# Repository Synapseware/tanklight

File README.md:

tanklights
==========

Tanklights is a fun project for adding moonlight lighting effects to a fish tank, or other environment where having an undulating lighting effect is desirable.  When properly laid out, the lighting is meant to be a rough simulation of what moonlight might look like under water.

The hardware/LEDs are wired up in a charlieplexed format.  Using just 3 pins of the micro controller (an Atmel ATTiny13), 6 LEDs can be individually controller.

The formula for the total number of LEDs is given by n^2-n, where n is the number of pins.  So, 3^2-3 = 6.

Read more about charlieplexing here: https://en.wikipedia.org/wiki/Charlieplexing

The lighting effects are accomplished by very fast switching of the LED matrix, so that persistence of vision plays a key role in the apparent light levels of the LEDs.

## building
The project has a simple Makefile.  It is currently configured to compiled under Linux only (but could be easily modified for other operating systems).  You will need to install AVRA, which is the open source equivalent of the Atmel AVR Assembler, avrasm.exe, that is included with AVR Studio for Windows.

### AVRA
Avra can also be installed easily on Linux:  `apt install -y avra` for Debian based systems.  The AVRA project home is here: http://avra.sourceforge.net/

### Atmel AVR Assembler
http://www.atmel.com/webdoc/avrassembler/index.html

### Other notes
The main idea with this project is not to build yet another LED blinking hello-world type of application, but is more a demonstration of what you can build using assembly and very lower powered micro-controllers.  Current code size is 640 bytes, or 320 words.  The timers on the ATTiny13 are used to advance or cycle through the lighting pattern, while the main charlieplexing display driver code is left to run at full speed.

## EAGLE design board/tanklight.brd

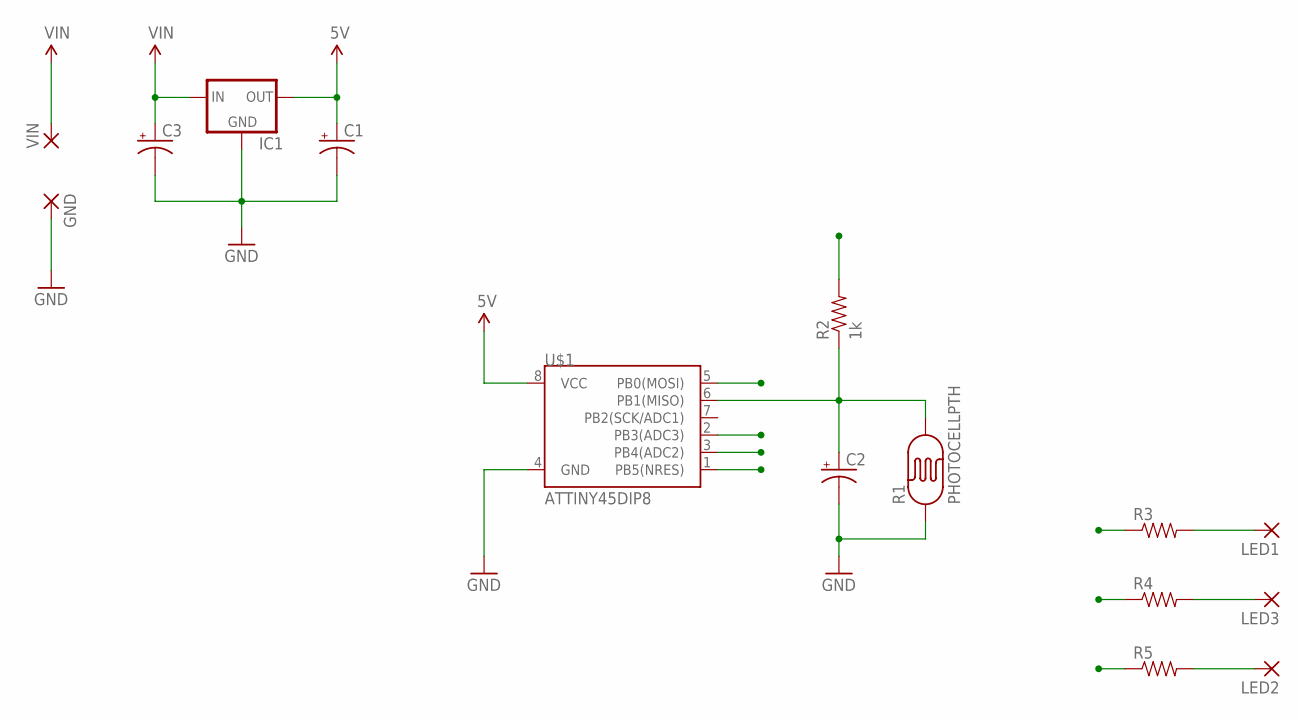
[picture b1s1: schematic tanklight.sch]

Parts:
C1, C3: CAP_POLPTH2; CPOL-RADIAL-10UF-25V
C2: CAP_POLPTH1; CPOL-RADIAL-100UF-25V
GND: 2,54/1,0
IC1: V_REG_78XXSINK; TO220-IGO
LED1, LED2, LED3: 2,54/1,0
R1: PHOTOCELLPTH; PHOTOCELL
R2: 1k; AXIAL-0.4
R3, R4, R5: RESISTORPTH-1/4W; AXIAL-0.4
U$1: ATTINY45DIP8; DIP08
VIN: 2,54/1,0

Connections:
5V: C1.1 (+), IC1.OUT, R2.P$2 (2), U$1.1 (PB5(NRES)), U$1.8 (VCC)
GND: C1.2 (-), C2.2 (-), C3.2 (-), GND.1, IC1.GND, R1.1, U$1.4 (GND)
LED1: R3.P$1 (1), U$1.5 (PB0(MOSI))
LED2: R5.P$1 (1), U$1.3 (PB4(ADC2))
LED3: R4.P$1 (1), U$1.2 (PB3(ADC3))
unnamed: C2.1 (+), R1.2, R2.P$1 (1), U$1.6 (PB1(MISO))
unnamed: LED1.1, R3.P$2 (2)
unnamed: LED3.1, R4.P$2 (2)
unnamed: LED2.1, R5.P$2 (2)
VIN: C3.1 (+), IC1.IN, VIN.1

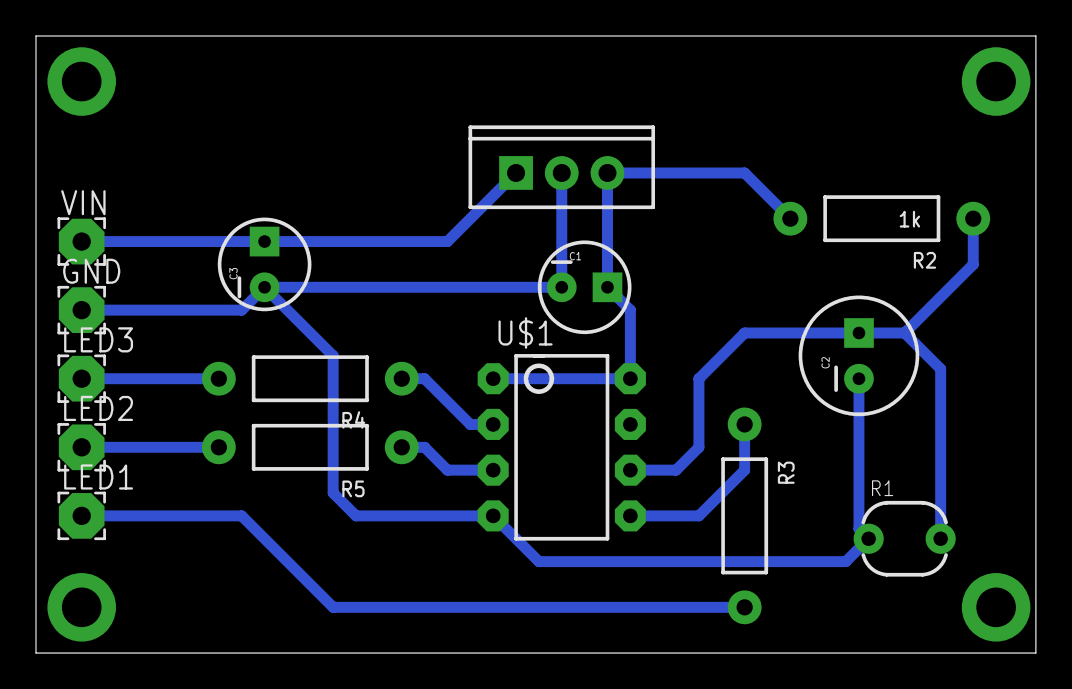
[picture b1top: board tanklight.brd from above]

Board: 2 copper layers, 55.5 x 34.3 mm, 15 parts (0 on the bottom side), 10 nets.

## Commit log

2014-06-03 Adding media
2017-03-16 Initial pass of converting to AVRA
2017-03-16 Adding readme and eagle project file
2017-03-16 Readme updates
2017-03-20 Reformatting data block
    New way of entering a block of data

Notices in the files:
parts and their libraries:
SparkFun-DigitalIC: Licensing: CC v3.0 Share-Alike You are welcome to use this library for commercial purposes.
